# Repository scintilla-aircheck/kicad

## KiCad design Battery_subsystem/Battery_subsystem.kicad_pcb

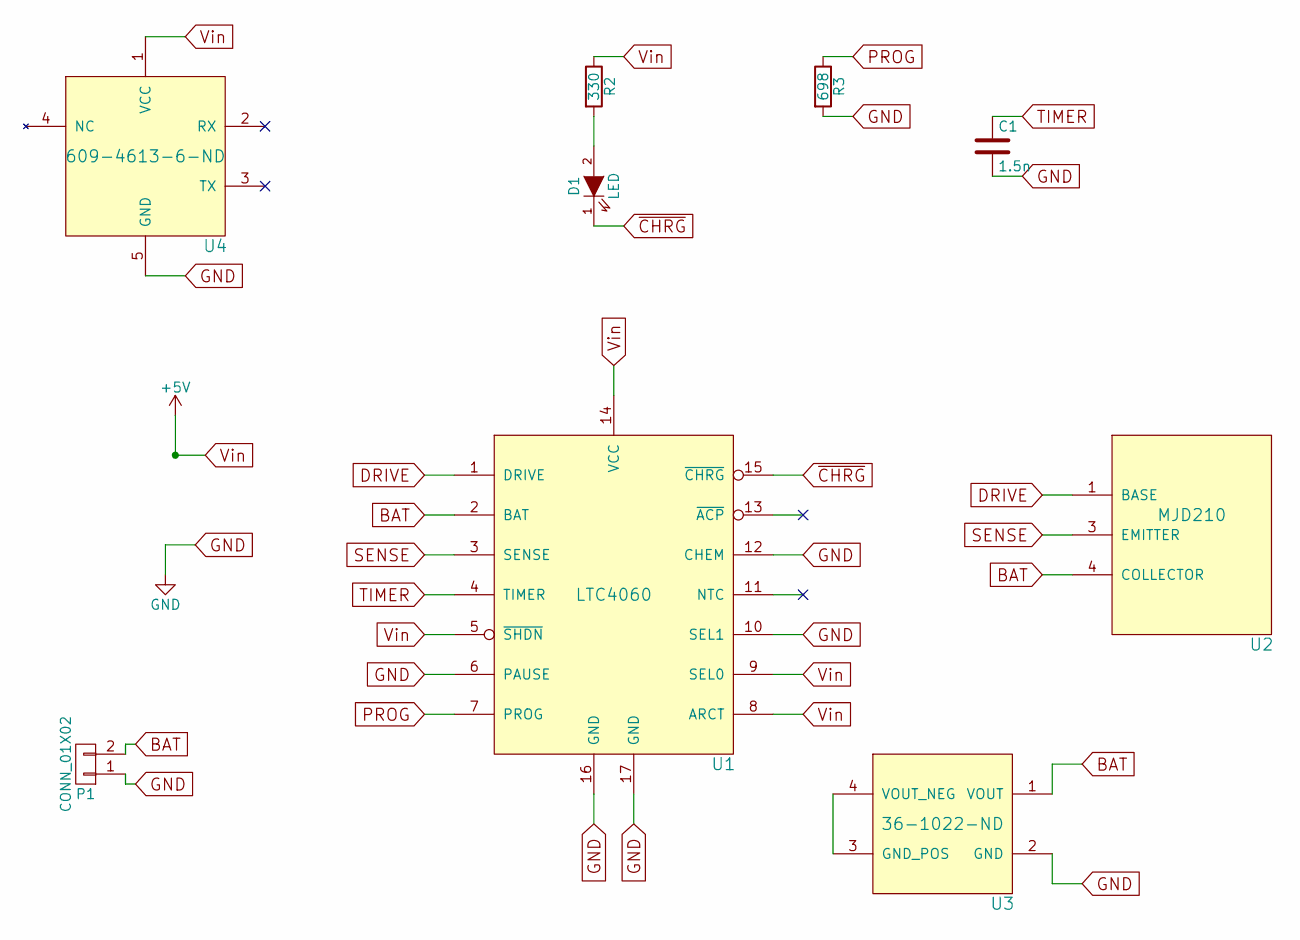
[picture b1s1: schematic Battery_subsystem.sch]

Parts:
C1: 1.5n; C_0805
D1: LED; LED_0805
P1: CONN_01X02; Socket_Strip_Straight_1x02
R2: 330; R_0805
R3: 698; R_0805
U1: LTC4060
U2: MJD210
U3: 36-1022-ND
U4: 609-4613-6-ND

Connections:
BAT: P1.2, U1.2 (BAT), U2.4 (COLLECTOR), U3.1 (VOUT)
DRIVE: U1.1 (DRIVE), U2.1 (BASE)
GND: C1.2, P1.1, R3.2, U1.6 (PAUSE), U1.10 (SEL1), U1.12 (CHEM), U1.16 (GND), U1.17 (GND), U3.2 (GND), U4.5 (GND)
unnamed: D1.2 (A), R2.2
unnamed: U3.3 (GND_POS), U3.4 (VOUT_NEG)
PROG: R3.1, U1.7 (PROG)
SENSE: U1.3 (SENSE), U2.3 (EMITTER)
TIMER: C1.1, U1.4 (TIMER)
Vin: R2.1, U1.5 (~SHDN), U1.8 (ARCT), U1.9 (SEL0), U1.14 (VCC), U4.1 (VCC)
~CHRG: D1.1 (K), U1.15 (~CHRG)

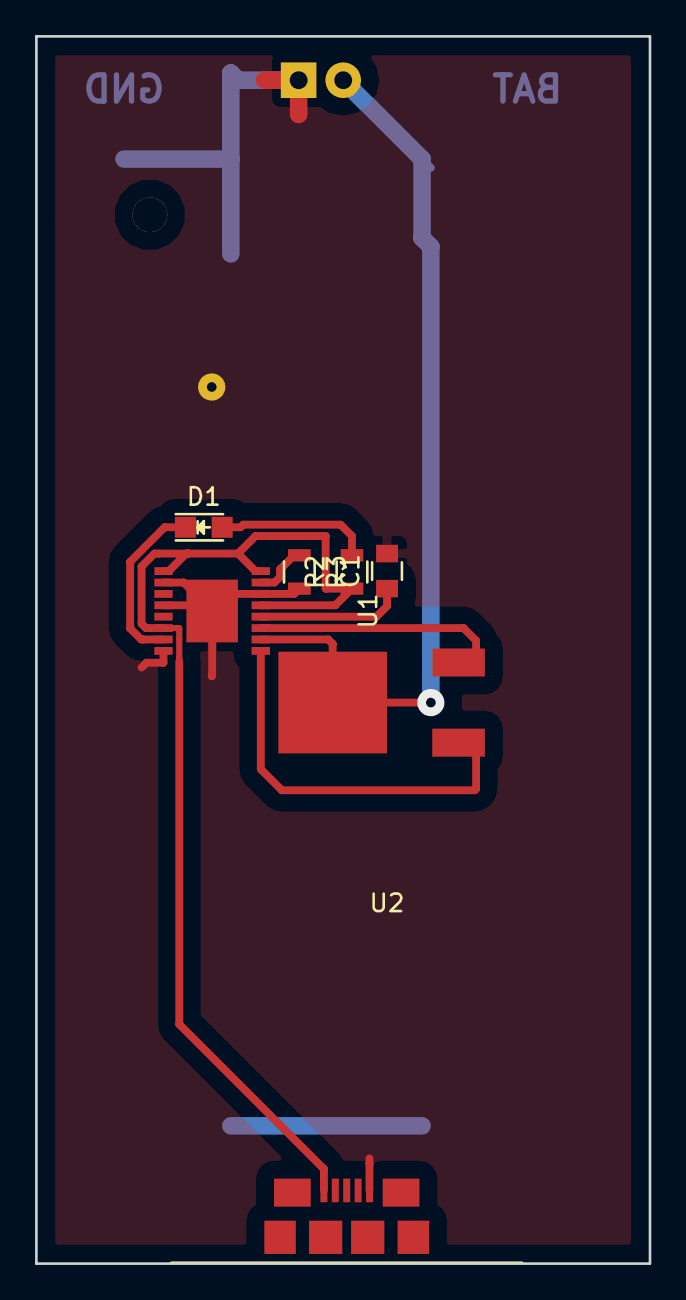
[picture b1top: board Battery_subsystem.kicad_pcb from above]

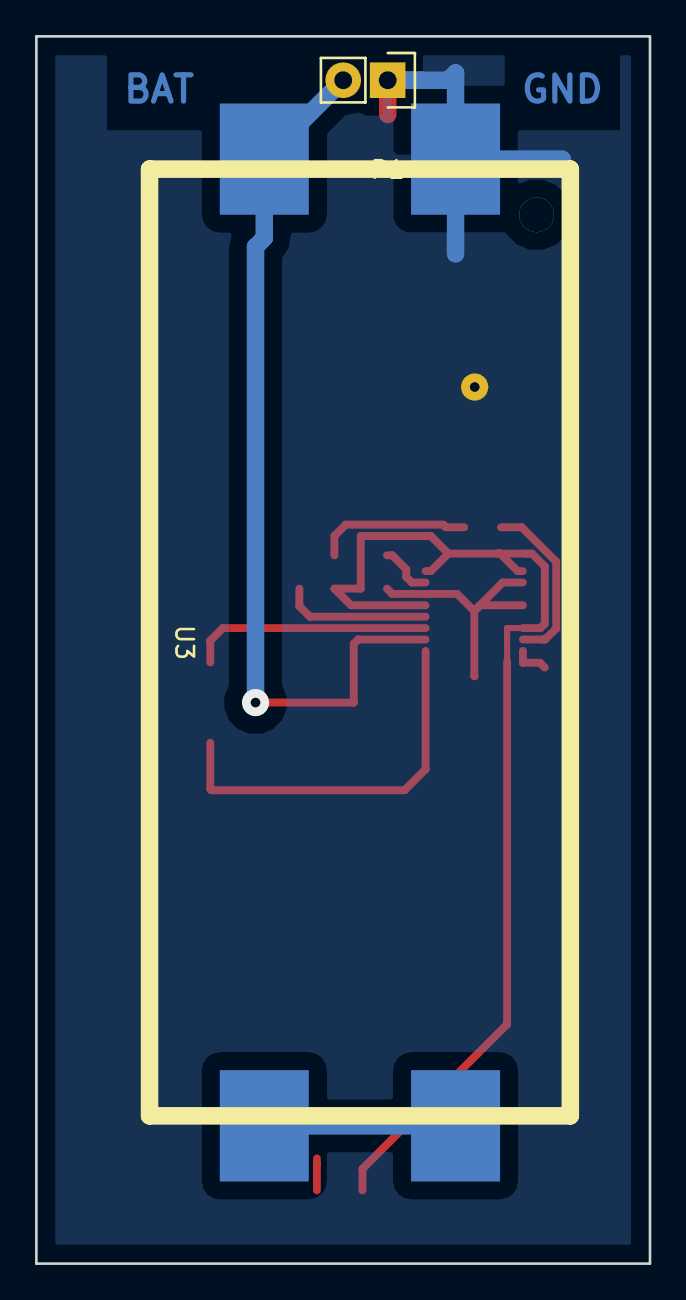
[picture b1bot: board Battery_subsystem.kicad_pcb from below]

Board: 2 copper layers, 35.0 x 70.0 mm, 9 parts (2 on the bottom side), 10 nets.

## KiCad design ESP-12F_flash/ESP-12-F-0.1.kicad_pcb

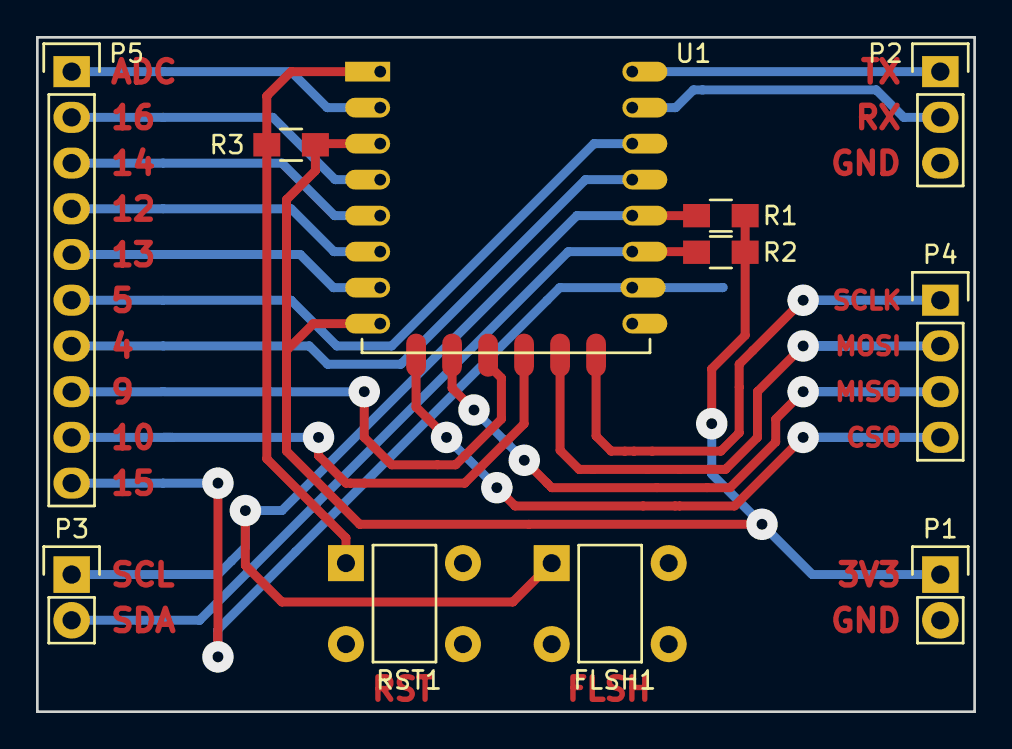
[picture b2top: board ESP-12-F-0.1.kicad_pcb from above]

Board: 2 copper layers, 52.1 x 37.5 mm, 12 parts (1 on the bottom side), 21 nets.

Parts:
FLSH1: SW_PUSH; 1825910-6
P1: PWR_CONN; Pin_Header_Straight_1x02
P2: UART_BUS; Pin_Header_Straight_1x03
P3: I2C_BUS; Pin_Header_Straight_1x02
P4: SPI_BUS; Pin_Header_Straight_1x04
P5: GPIO_CONN; Pin_Header_Straight_1x10
R1, R2: 4k7; R_0805_HandSoldering
R3, R4: 10k; R_0805_HandSoldering
RST1: SW_PUSH; 1825910-6
U1: ESP-12F

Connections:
+3V3: P1.1, R1.1, R2.1, R3.1, U1.3, U1.8
/ADC: P5.1, U1.2
/CSO: P4.4, U1.9
/GPIO4: P5.7, U1.19
/GPIO5: P5.6, U1.20
/GPIO9: P5.8, U1.11
/GPIO10: P5.9, U1.12
/GPIO12: P5.4, U1.6
/GPIO13: P5.5, U1.7
/GPIO14: P5.3, U1.5
/GPIO15: P5.10, R4.1, U1.16
/GPIO16: P5.2, U1.4
/MISO: P4.3, U1.10
/MOSI: P4.2, U1.13
/RESET: R3.2, RST1.1, U1.1
/RX: P2.2, U1.21
/SCL: FLSH1.1, P3.1, R1.2, U1.18
/SCLK: P4.1, U1.14
/SDA: P3.2, R2.2, U1.17
/TX: P2.1, U1.22
GND: FLSH1.2, P1.2, P2.3, R4.2, RST1.2, U1.15

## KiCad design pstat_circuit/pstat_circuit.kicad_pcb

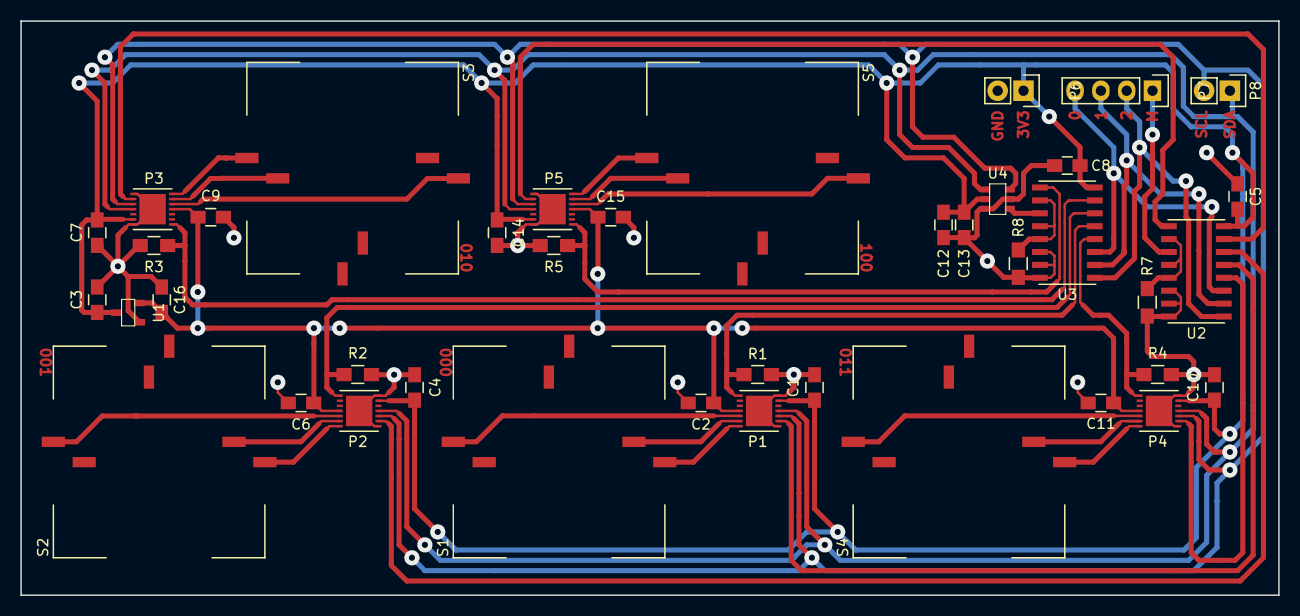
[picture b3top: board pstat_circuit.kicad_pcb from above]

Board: 2 copper layers, 123.8 x 56.5 mm, 40 parts (0 on the bottom side), 37 nets.

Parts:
C1, C2, C3, C4, C5, C6, C7, C8, C9, C10, C11, C13, C14, C15, C16: 0.1uF; C_0805_HandSoldering
C12: 10uF; C_0805_HandSoldering
P1, P2, P3, P4, P5: LMP91000-2; LMP91000
P6: PWR_BUS; Pin_Header_Straight_1x02
P7: PSTAT_CTRL; Pin_Header_Straight_1x04
P8: I2C_BUS; Pin_Header_Straight_1x02
R1, R2, R3, R4, R5, R7, R8: 10K; R_0805_HandSoldering
S1, S2, S3, S4, S5: SPEC-2; SPEC_pinned
U1: MCP1700-2; MCP1700
U2, U3: CD4051BM96-2; CD4051BM96
U4: MCP3425-2; MCP3425

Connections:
+2V5: C2.1, C6.1, C9.1, C11.1, C15.1, C16.1, P1.11, P2.11, P3.11, P4.11, P5.11, U1.2
+3V3: C1.1, C3.2, C4.1, C5.1, C7.1, C8.1, C10.1, C12.1, C13.2, C14.1, P1.6, P2.6, P3.6, P4.6, P5.6, P6.1, U1.3, U2.16, U3.16, U4.5
/MENB: P7.1, U2.3
/PSEL0: P7.4, U2.11, U3.11
/PSEL1: P7.3, U2.10, U3.10
/PSEL2: P7.2, U2.9, U3.9
/SCL: P1.3, P2.3, P3.3, P4.3, P5.3, P8.2, U4.3
/SDA: P1.4, P2.4, P3.4, P4.4, P5.4, P8.1, U4.4
/VSTAT: U3.3, U4.1
GND: C1.2, C2.2, C3.1, C4.2, C5.2, C6.2, C7.2, C8.2, C9.2, C10.2, C11.2, C12.2, C13.1, C14.2, C15.2, C16.2, P1.1, P1.7, P1.DAP, P2.1, P2.7, P2.DAP, P3.1, P3.7, P3.DAP, P4.1, P4.7, P4.DAP, P5.1, P5.7, P5.DAP, P6.2, R1.2, R2.2, R3.2, R4.2, R5.2, R7.1, R8.1, U1.1, U2.6, U2.7, U2.8, U3.6, U3.7, U3.8, U4.2, U4.6
unnamed: P1.2, U2.13
unnamed: P1.8, R1.1, U3.13
unnamed: P1.12, S1.1
unnamed: P1.13, S1.4
unnamed: P1.14, S1.5
unnamed: P2.2, U2.14
unnamed: P2.8, R2.1, U3.14
unnamed: P2.12, S2.1
unnamed: P2.13, S2.4
unnamed: P2.14, S2.5
unnamed: P3.2, U2.15
unnamed: P3.8, R3.1, U3.15
unnamed: P3.12, S3.1
unnamed: P3.13, S3.4
unnamed: P3.14, S3.5
unnamed: P4.2, U2.12
unnamed: P4.8, R4.1, U3.12
unnamed: P4.12, S4.1
unnamed: P4.13, S4.4
unnamed: P4.14, S4.5
unnamed: P5.2, U2.1
unnamed: P5.8, R5.1, U3.1
unnamed: P5.12, S5.1
unnamed: P5.13, S5.4
unnamed: P5.14, S5.5
unnamed: R7.2, U2.2, U2.4, U2.5
unnamed: R8.2, U3.2, U3.4, U3.5

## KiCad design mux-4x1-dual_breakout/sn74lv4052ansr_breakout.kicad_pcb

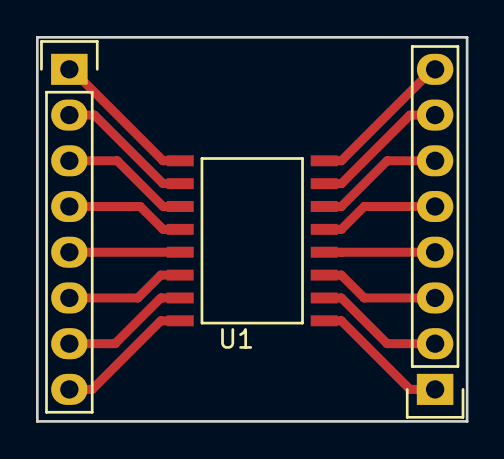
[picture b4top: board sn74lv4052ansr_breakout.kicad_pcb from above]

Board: 2 copper layers, 23.9 x 21.3 mm, 3 parts (0 on the bottom side), 16 nets.

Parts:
P1, P2: CONN_01X08; Pin_Header_Straight_1x08
U1: SN74LV4052ANSR

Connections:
unnamed: P1.1, U1.1
unnamed: P1.2, U1.2
unnamed: P1.3, U1.3
unnamed: P1.4, U1.4
unnamed: P1.5, U1.5
unnamed: P1.6, U1.6
unnamed: P1.7, U1.7
unnamed: P1.8, U1.8
unnamed: P2.1, U1.9
unnamed: P2.2, U1.10
unnamed: P2.3, U1.11
unnamed: P2.4, U1.12
unnamed: P2.5, U1.13
unnamed: P2.6, U1.14
unnamed: P2.7, U1.15
unnamed: P2.8, U1.16

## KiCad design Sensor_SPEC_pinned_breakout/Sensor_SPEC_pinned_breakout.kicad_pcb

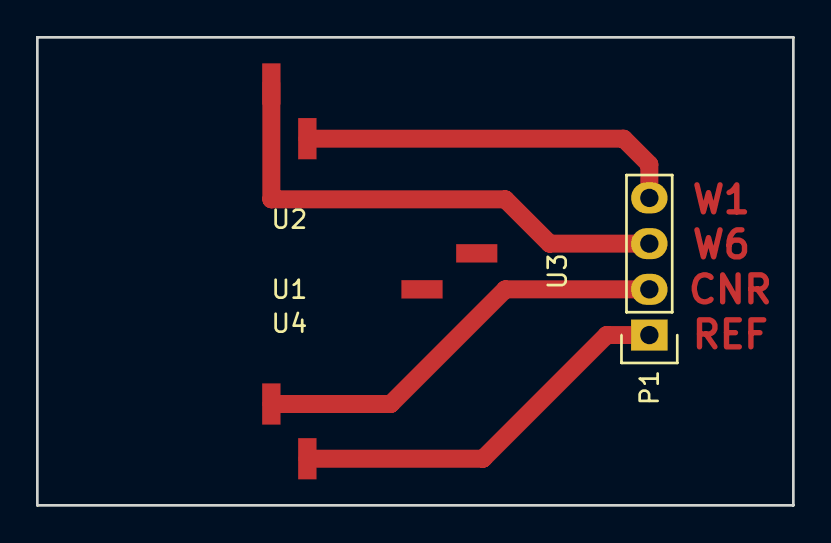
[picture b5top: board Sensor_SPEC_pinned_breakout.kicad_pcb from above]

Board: 2 copper layers, 42.0 x 26.0 mm, 5 parts (0 on the bottom side), 4 nets.

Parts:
P1: CONN_01X04; Socket_Strip_Straight_1x04
U1: SPEC; SPEC_pinned
U2, U3, U4: SMM-102-02-S-S

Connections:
COUNTER: P1.2, U4.1
REFERENCE: P1.1, U4.2
WORKING_1: P1.4, U2.1
WORKING_6: P1.3, U2.2

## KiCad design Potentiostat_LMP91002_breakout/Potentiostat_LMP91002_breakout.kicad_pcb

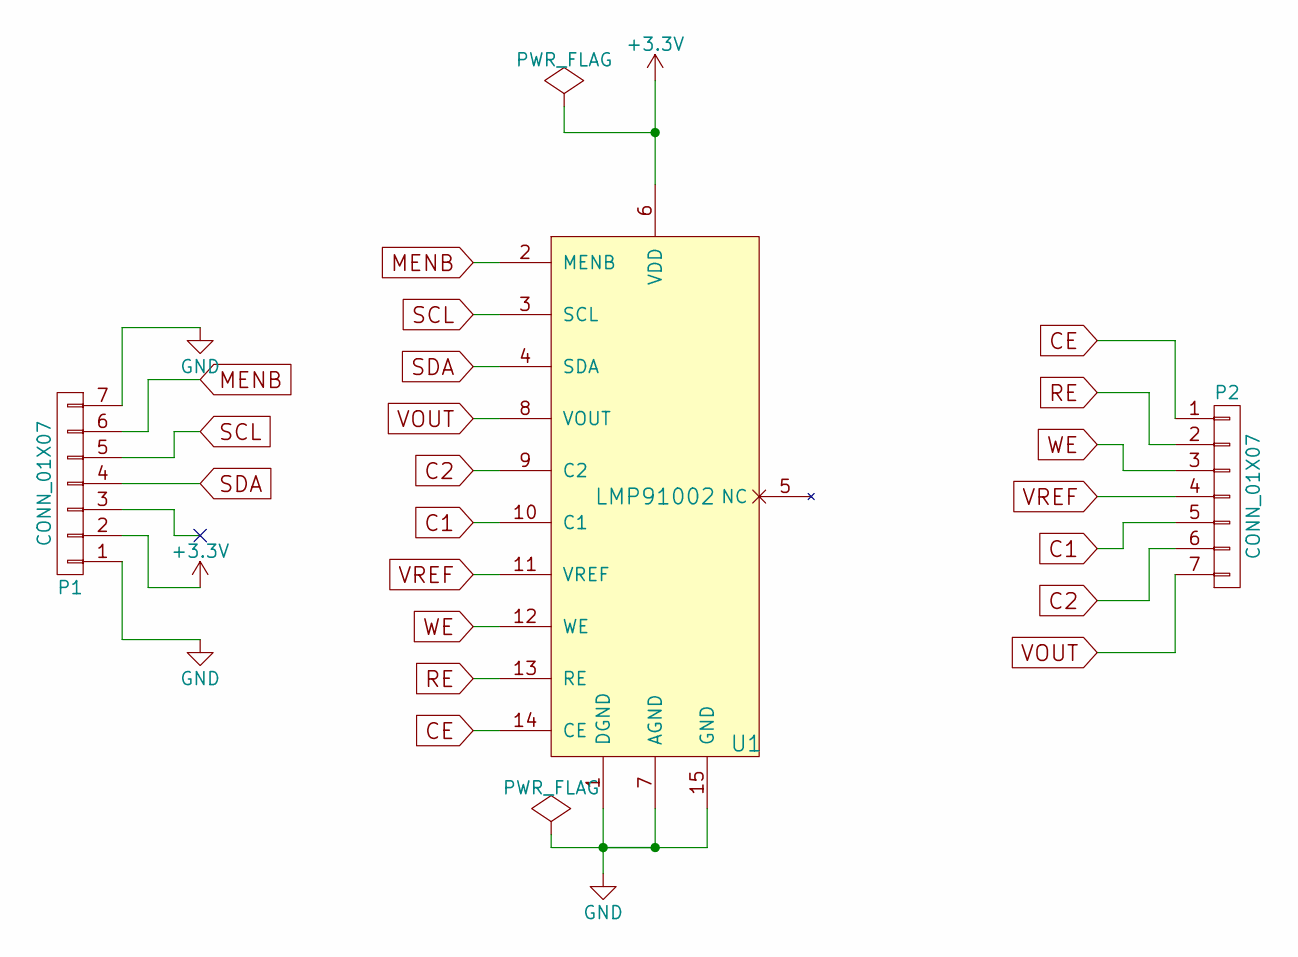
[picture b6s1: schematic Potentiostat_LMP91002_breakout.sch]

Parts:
P1, P2: CONN_01X07; Pin_Header_Straight_1x07
U1: LMP91002

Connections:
+3V3: P1.2, U1.6 (VDD)
C1: P2.5, U1.10 (C1)
C2: P2.6, U1.9 (C2)
CE: P2.1, U1.14 (CE)
GND: P1.1, P1.7, U1.1 (DGND), U1.7 (AGND), U1.15 (GND)
MENB: P1.6, U1.2 (MENB)
RE: P2.2, U1.13 (RE)
SCL: P1.5, U1.3 (SCL)
SDA: P1.4, U1.4 (SDA)
VOUT: P2.7, U1.8 (VOUT)
VREF: P2.4, U1.11 (VREF)
WE: P2.3, U1.12 (WE)

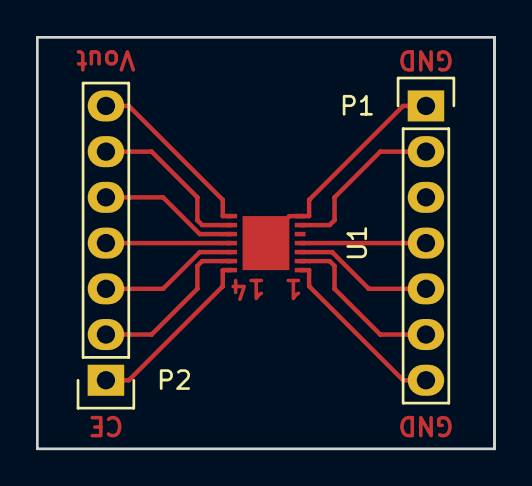
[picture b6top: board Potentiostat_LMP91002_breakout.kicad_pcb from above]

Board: 2 copper layers, 25.4 x 22.9 mm, 3 parts (0 on the bottom side), 12 nets.

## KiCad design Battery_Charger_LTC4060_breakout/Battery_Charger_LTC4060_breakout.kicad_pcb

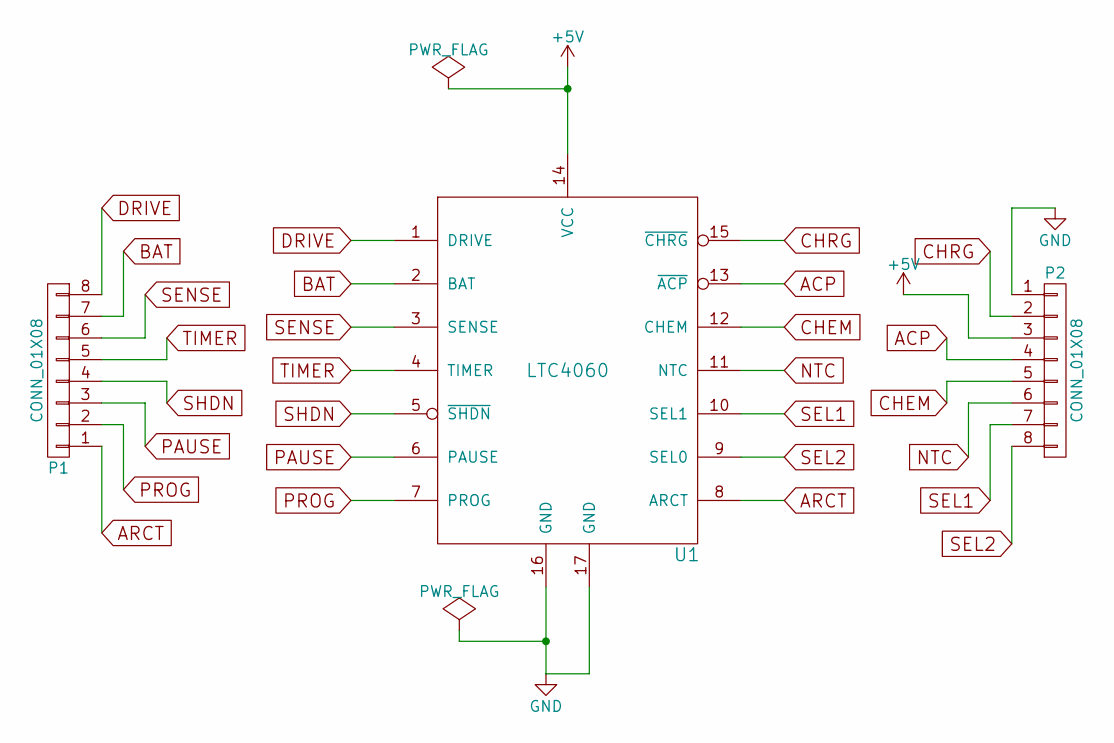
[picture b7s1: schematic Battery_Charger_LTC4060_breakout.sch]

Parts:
P1, P2: CONN_01X08; Pin_Header_Straight_1x08
U1: LTC4060

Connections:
+5V: P2.3, U1.14 (VCC)
ACP: P2.4, U1.13 (~ACP)
ARCT: P1.1, U1.8 (ARCT)
BAT: P1.7, U1.2 (BAT)
CHEM: P2.5, U1.12 (CHEM)
CHRG: P2.2, U1.15 (~CHRG)
DRIVE: P1.8, U1.1 (DRIVE)
GND: P2.1, U1.16 (GND), U1.17 (GND)
NTC: P2.6, U1.11 (NTC)
PAUSE: P1.3, U1.6 (PAUSE)
PROG: P1.2, U1.7 (PROG)
SEL1: P2.7, U1.10 (SEL1)
SEL2: P2.8, U1.9 (SEL0)
SENSE: P1.6, U1.3 (SENSE)
SHDN: P1.4, U1.5 (~SHDN)
TIMER: P1.5, U1.4 (TIMER)

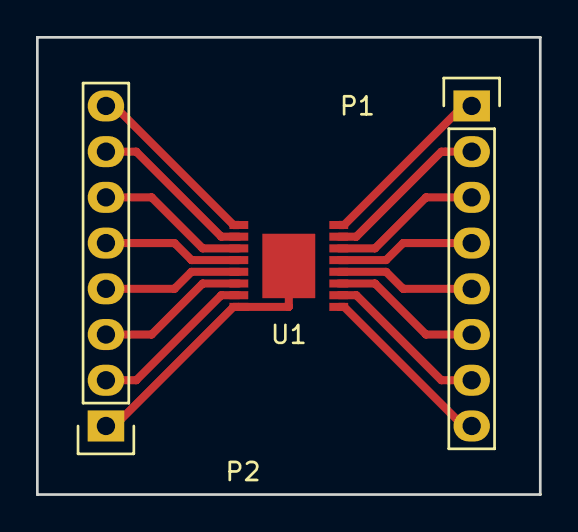
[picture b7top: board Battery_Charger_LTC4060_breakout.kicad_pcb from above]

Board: 2 copper layers, 27.9 x 25.4 mm, 3 parts (0 on the bottom side), 16 nets.

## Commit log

2016-07-28 added gerbers for skm61
2016-08-02 added a few more breakout board projects
2016-08-02 added .gitignore
2016-08-02 updated the location of the scintilla library
2016-08-25 Add basic ESP-12F breakout schematic
2016-08-25 Add ESP-12F flash schematic
2016-08-26 Add missing pull-down/pull-up resistors and remove useless EN switch
2016-08-26 added a bunch of stuff
2016-08-26 Add LMP91000 component schematic
2016-08-26 Start basic SPEC/PSTAT breakout board
2016-08-26 added SPEC and SMM-102-02-S-S
2016-09-02 changed SPEC pinned breakout
2016-09-02 Do some stuff
2016-09-13 fix for esp-12f
2016-09-13 Add TI 8x1 and 4x2 mux/demux and reconfigure ESP-12F schematic
2016-09-14 Add dual 4:1 mux breakout
2016-09-15 added battery subsystem
2016-09-15 Commit WIP master board schematic
2016-09-20 Add 95% of pcb design for PSTAT circuit
2016-09-20 Finish first draft of PSTAT pcb
2016-09-20 Rotate PCB design
2016-09-21 Minor changes to PSTAT breakout
2016-09-21 Replace 10K ohm load resistor with 0.1uF capacitor on 2V5 output of MCP1700
2016-09-26 Widen traces on pstat breakout
2016-09-28 Remove deadend trace
2016-09-29 Update ESP-12-F flash breakout to isolate I2C pins
2016-09-29 added humidity sensor
